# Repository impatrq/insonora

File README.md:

<div align="center">

# Proyecto Insonora - IMPA TRQ

&nbsp;

| Página web | Email | Instagram |
|------------|-------|-----------|
|[Insonora Web](https://arriolan.github.io/insonora.github.io/)|insonora.impatrq@gmail.com|[@proyecto_insonora](https://www.instagram.com/proyecto_insonora)|

&nbsp;

</div>

## ¿Qué es Insonora?

Insonora es un sistema capaz de disminuir el ruido del ambiente.
Enfocado a personas con TEA e 
hipersensibilidad auditiva.
Utilizando el principio de cancelación activa de sonido.

## ¿Como Funciona?

La cancelación activa de sonido funciona mediante la generación de ondas sonoras opuestas a las ondas de sonido no deseado, lo que resulta en la cancelación o atenuación del ruido.

## ¿Quiénes somos?

Somos un grupo de alumnos de E.E.S.T. N°7 "Taller Regional Quilmes" (IMPA).

### Arriola, Nicolas Agustin
* 📷 Instagram: _nicoarriola

* 📧 arriolanicolas21@gmail.com

* LinkedIn: 

### Camdessus, Franco
* 📷 Instagram: fran.camdessus

* 📧 francocamdessus@gmail.com

* LinkedIn: https://www.linkedin.com/in/franco-camdessus-175991275/

### Luna, Thiago
* 📷 Instagram: thiago.lunaa

* 📧 

* LinkedIn: https://www.linkedin.com/in/thiago-luna-5606a8272/

### Guida, Dylan Ulises
* 📷 Instagram: dy.guida

* 📧 guidad475@gmail.com

* LinkedIn: https://www.linkedin.com/in/dylan-guida-2a4480258/

### Weinzettel, Dylan
* 📷 Instagram: dylan_zeq

* 📧 weinzettel.dylan@hotmail.com
  
* LinkedIn: https://www.linkedin.com/in/dylan-weinzettel-9874b429a/

<div align="center">

</div>

## ¿Cómo contactarnos?

* 📧 Email: insonora.impatrq@gmail.com

* 🌐 Página Web: https://arriolan.github.io/insonora.github.io/

* 📷 Instagram: @proyecto_insonora

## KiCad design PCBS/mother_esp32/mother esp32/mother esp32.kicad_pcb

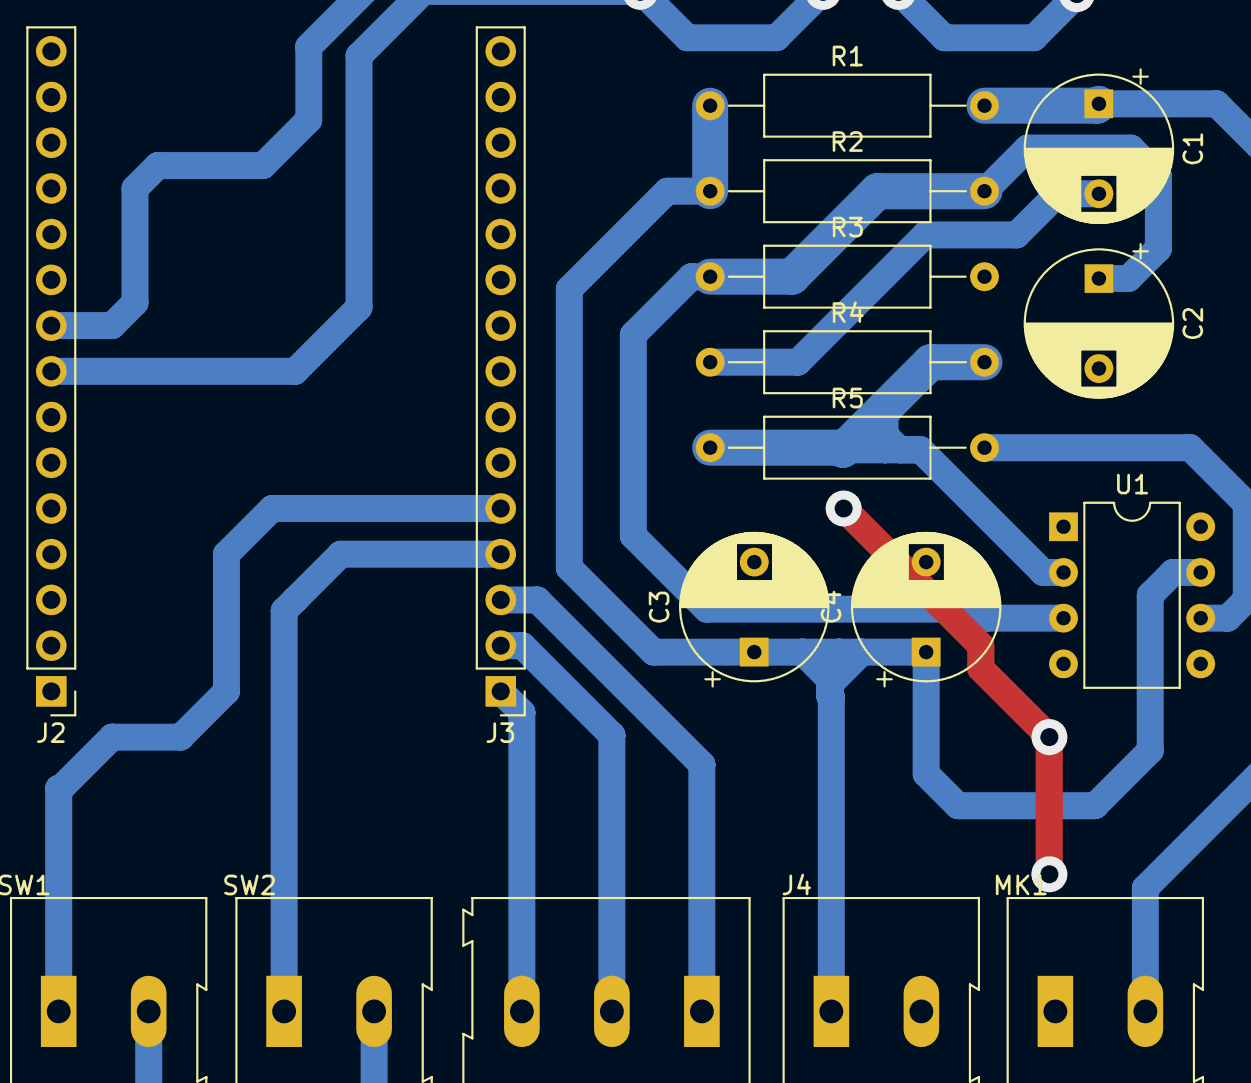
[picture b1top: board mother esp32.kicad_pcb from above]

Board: 2 copper layers, 17 parts (0 on the bottom side), 13 nets.

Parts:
C1: 1uf; CP_Radial_D8.0mm_P5.00mm
C2: 10uf; CP_Radial_D8.0mm_P5.00mm
C3: 10uF; CP_Radial_D8.0mm_P5.00mm
C4: 460uf; CP_Radial_D8.0mm_P5.00mm
J2, J3: Conn_01x15_Pin; PinHeader_1x15_P2.54mm_Vertical
J4: Screw_Terminal_01x02; TerminalBlock_Altech_AK300-2_P5.00mm
J6: matriz; TerminalBlock_Altech_AK300-3_P5.00mm
MK1: Microphone; TerminalBlock_Altech_AK300-2_P5.00mm
R1, R4: 10k; R_Axial_DIN0309_L9.0mm_D3.2mm_P15.24mm_Horizontal
R2, R3, R5: 100k; R_Axial_DIN0309_L9.0mm_D3.2mm_P15.24mm_Horizontal
SW1: switch 1; TerminalBlock_Altech_AK300-2_P5.00mm
SW2: switch 2; TerminalBlock_Altech_AK300-2_P5.00mm
U1: TL071; DIP-8_W7.62mm

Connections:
3.3v: SW1.2, SW2.2
+3.3V: C3.1, C4.1, J4.1, R1.1, R2.1, U1.7 (V+)
GND: C2.2, C3.2, C4.2, J4.2, MK1.1 (-), R3.2, U1.4 (V-)
unnamed: J3.1, J6.3
unnamed: J3.3, J6.1
unnamed: J3.2, J6.2
unnamed: C1.2, R4.1
unnamed: C1.1, MK1.2 (+), R1.2
unnamed: C2.1, R2.2, R3.1, U1.3 (+)
unnamed: R4.2, R5.1, U1.2 (-)
d2: J3.4, SW2.1
d4: J3.5, SW1.1
d33: R5.2, U1.6

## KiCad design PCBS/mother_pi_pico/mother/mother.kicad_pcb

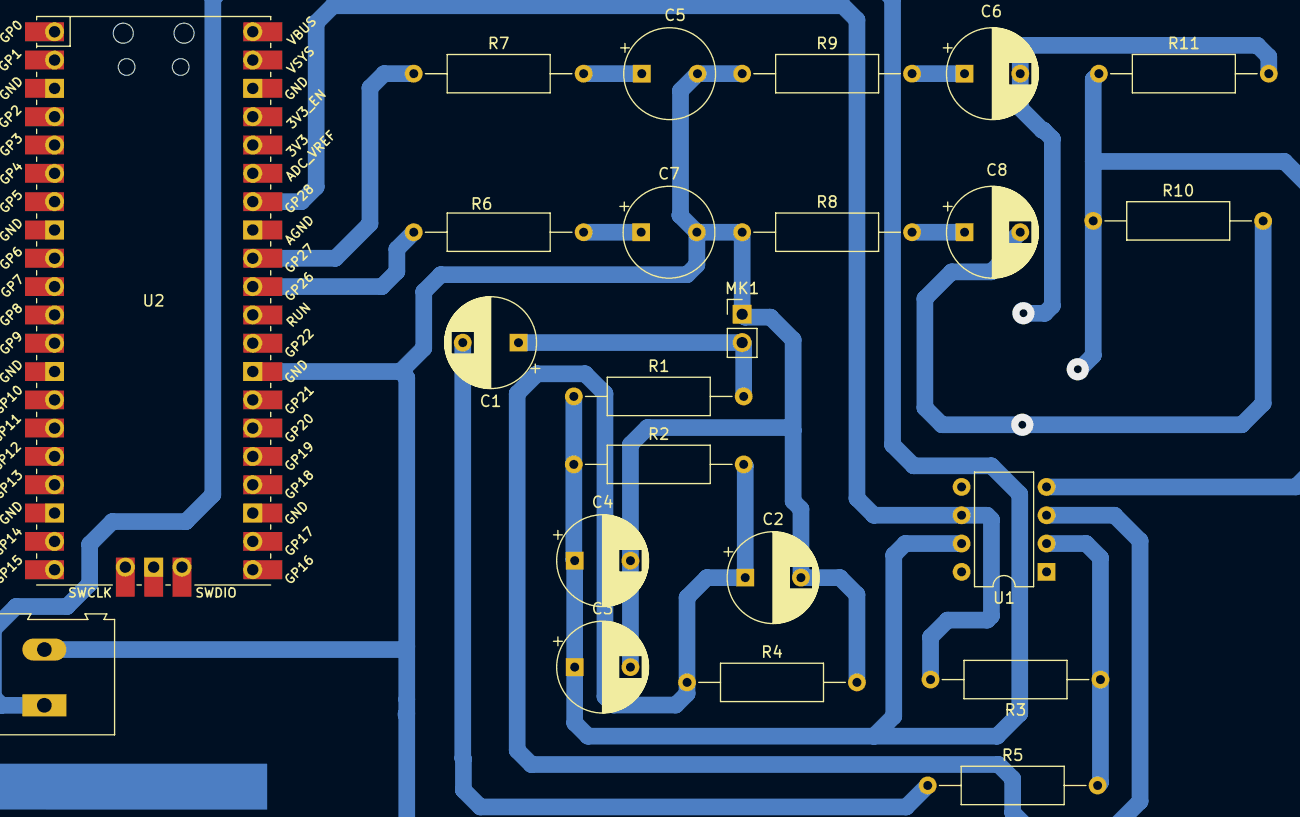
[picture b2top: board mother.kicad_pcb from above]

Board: 2 copper layers, 23 parts (0 on the bottom side), 13 nets.

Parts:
C1: 1uf; CP_Radial_D8.0mm_P5.00mm
C2: 10uf; CP_Radial_D8.0mm_P5.00mm
C3: 10uF; CP_Radial_D8.0mm_P5.00mm
C4: 460uf; CP_Radial_D8.0mm_P5.00mm
C5, C7: 100nF; CP_Radial_Tantal_D8.0mm_P5.00mm
C6, C8: 47uF; CP_Radial_D8.0mm_P5.00mm
J2: Screw_Terminal_01x02; TerminalBlock_Altech_AK300-2_P5.00mm
MK1: Microphone; PinHeader_1x02_P2.54mm_Vertical
R1, R5: 10k; R_Axial_DIN0309_L9.0mm_D3.2mm_P15.24mm_Horizontal
R2, R3, R4: 100k; R_Axial_DIN0309_L9.0mm_D3.2mm_P15.24mm_Horizontal
R6, R7: 220; R_Axial_DIN0309_L9.0mm_D3.2mm_P15.24mm_Horizontal
R8, R9: 100; R_Axial_DIN0309_L9.0mm_D3.2mm_P15.24mm_Horizontal
R10, R11: 1,8k; R_Axial_DIN0309_L9.0mm_D3.2mm_P15.24mm_Horizontal
U1: TL071; DIP-8_W7.62mm
U2: Pico; RPi_Pico_SMD_TH

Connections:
+3.3V: C3.1, C4.1, J2.1, R1.1, R2.1, U1.7 (V+)
GND: C2.2, C3.2, C4.2, C5.2, C7.2, J2.2, MK1.1 (-), R4.2, R8.1, R9.1, R10.1, R11.1, U1.4 (V-), U2.28 (GND)
unnamed: C1.2, R5.1
unnamed: C5.1, C6.1, R7.2, R9.2
unnamed: C6.2, R11.2
unnamed: C7.1, C8.1, R6.2, R8.2
unnamed: C8.2, R10.2
unnamed: C1.1, MK1.2 (+), R1.2
unnamed: C2.1, R2.2, R4.1, U1.3 (+)
unnamed: R3.1, R5.2, U1.2 (-)
unnamed: R6.1, U2.31 (GPIO26_ADC0)
unnamed: R7.1, U2.32 (GPIO27_ADC1)
unnamed: R3.2, U1.6, U2.34 (GPIO28_ADC2)

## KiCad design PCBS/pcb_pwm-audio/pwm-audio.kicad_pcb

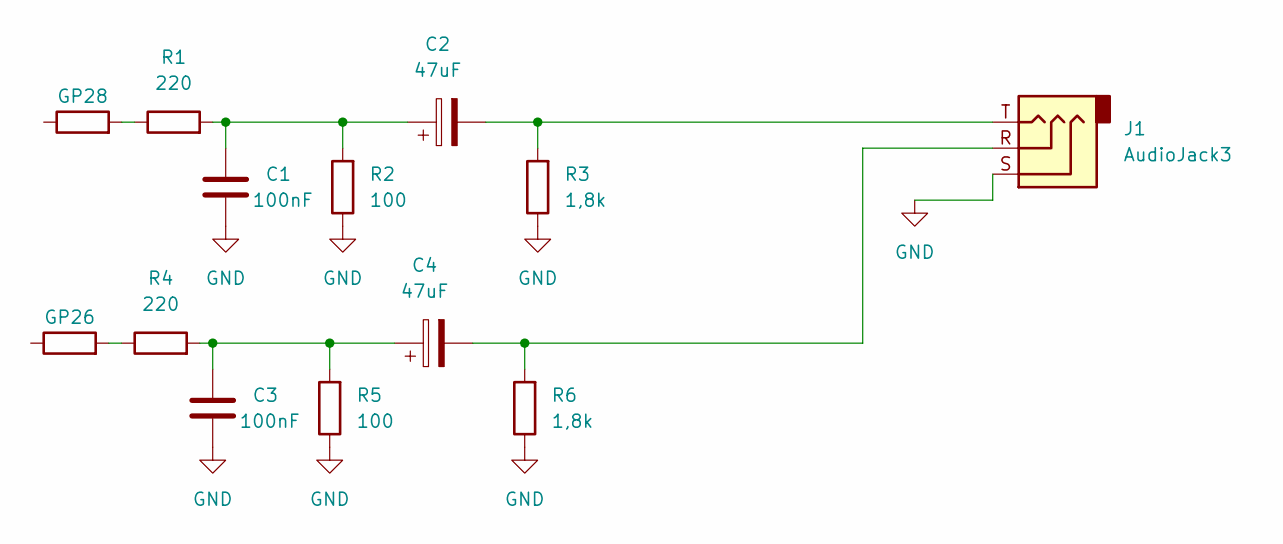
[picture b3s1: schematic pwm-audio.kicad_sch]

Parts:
C1, C3: 100nF; CP_Radial_D4.0mm_P2.00mm
C2, C4: 47uF; CP_Radial_D4.0mm_P1.50mm
GP26, GP28: PinHeader_1x02_P1.00mm_Vertical
J1: AudioJack3; Jack_3.5mm_CUI_SJ1-3525N_Horizontal
R1, R4: 220; R_Axial_DIN0204_L3.6mm_D1.6mm_P5.08mm_Horizontal
R2, R5: 100; R_Axial_DIN0204_L3.6mm_D1.6mm_P5.08mm_Horizontal
R3, R6: 1,8k; R_Axial_DIN0204_L3.6mm_D1.6mm_P5.08mm_Horizontal

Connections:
GND: C1.2, C3.2, J1.S, R2.1, R3.1, R5.1, R6.1
unnamed: C1.1, C2.1, R1.2, R2.2
unnamed: C2.2, J1.T, R3.2
unnamed: C3.1, C4.1, R4.2, R5.2
unnamed: C4.2, J1.R, R6.2
unnamed: GP26.2, R4.1
unnamed: GP28.2, R1.1

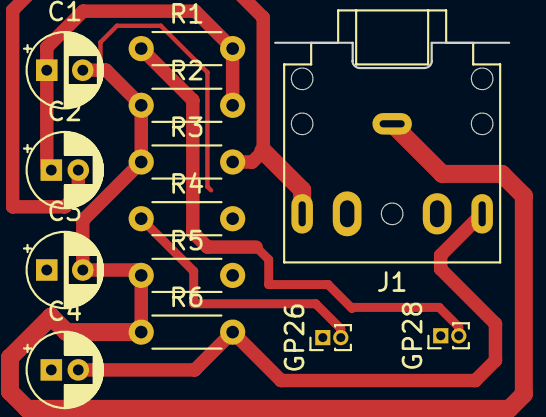
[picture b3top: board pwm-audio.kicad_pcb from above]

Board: 2 copper layers, 13 parts (0 on the bottom side), 7 nets.

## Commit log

2023-11-21 feat : Subir primer codigo de insonora en python
2023-11-21 feat : subir el codigo para generar un tono desfasado 180 grados en una raspberry pi pico usando la salida PWM
2023-11-21 feat : codigo reproduccion de audio en tiempo real en raspberry pi pico
2023-11-21 feat : subir codigo para generar tonos con el dac de la esp32
2023-11-21 feat : primeras pruebas separacion de canales DAC esp32
2023-11-21 feat : subir codigo para generar senoidales desfasadas ESP32 CWG
2023-11-21 feat : subir codigo para reproducir audio en tiempo real ESP32
2023-11-21 feat : subir codigo FFT arduino ESP32
2023-11-21 feat : subir archivos necesarios para el funcionamiento de el FFT
2023-11-21 feat : subir foto pcb pwm audio terminado, este no se uso en el prototipo final
2023-11-21 fix : muevo la foto a dentro de la carpeta FOTOS
2023-11-21 feat : subir foto de la fuente hecha por nosotros
2023-11-21 feat : pruebas esp32 dac senoidales
2023-11-21 feat : subir pruebas esp32 dac 2
2023-11-21 feat :: subir pcb preamp kikad
2023-11-21 feat : subir esquematico preamp kikad
2023-11-21 feat : subir pcb pwm-audio
2023-11-21 feat : subir esquematico pwm- audio kikad
2023-11-21 feat : primer foto pwm audio circuito
2023-11-21 feat : Subir presupuesto
2023-11-21 feat : Subir presupuesto 2
2023-11-21 feat : Subir presupuesto 3
2023-11-21 feat : Subir Compra Componentes
2023-11-22 Add files via upload
    casse de madera para insonora
2023-11-22 casse de madera para pcbs insonora
2023-11-22 paneles de insonorizacion
2023-11-22 corte de la caja de insonora para interaccion
2023-11-22 cortes de madera
2023-11-22 cortes plaquetas de cobre
2023-11-22 disposicion de parlantes
    casse de madera para insonora
2023-11-22 plano de insonora
    casse de madera para insonora
2023-11-22 presentacion insonora
2023-11-22 informe descriptivo
2023-11-22 compra y corte del acrilico
2023-11-24 feat:creacion div programacion
2023-11-24 feat: update codigos
2023-11-24 feaat: estructura
2023-11-24 feat:update
2023-11-24 feat : Subir post
2023-11-24 Fix : Actualizar nombre
2023-11-24 fix : pongo los links de linkedin menos el de arriola
2023-11-24 feat: agrego carpeta tecnica
2023-11-24 feat : Subir Carpeta Tecnica
2023-11-24 feat : Subir post de ig
